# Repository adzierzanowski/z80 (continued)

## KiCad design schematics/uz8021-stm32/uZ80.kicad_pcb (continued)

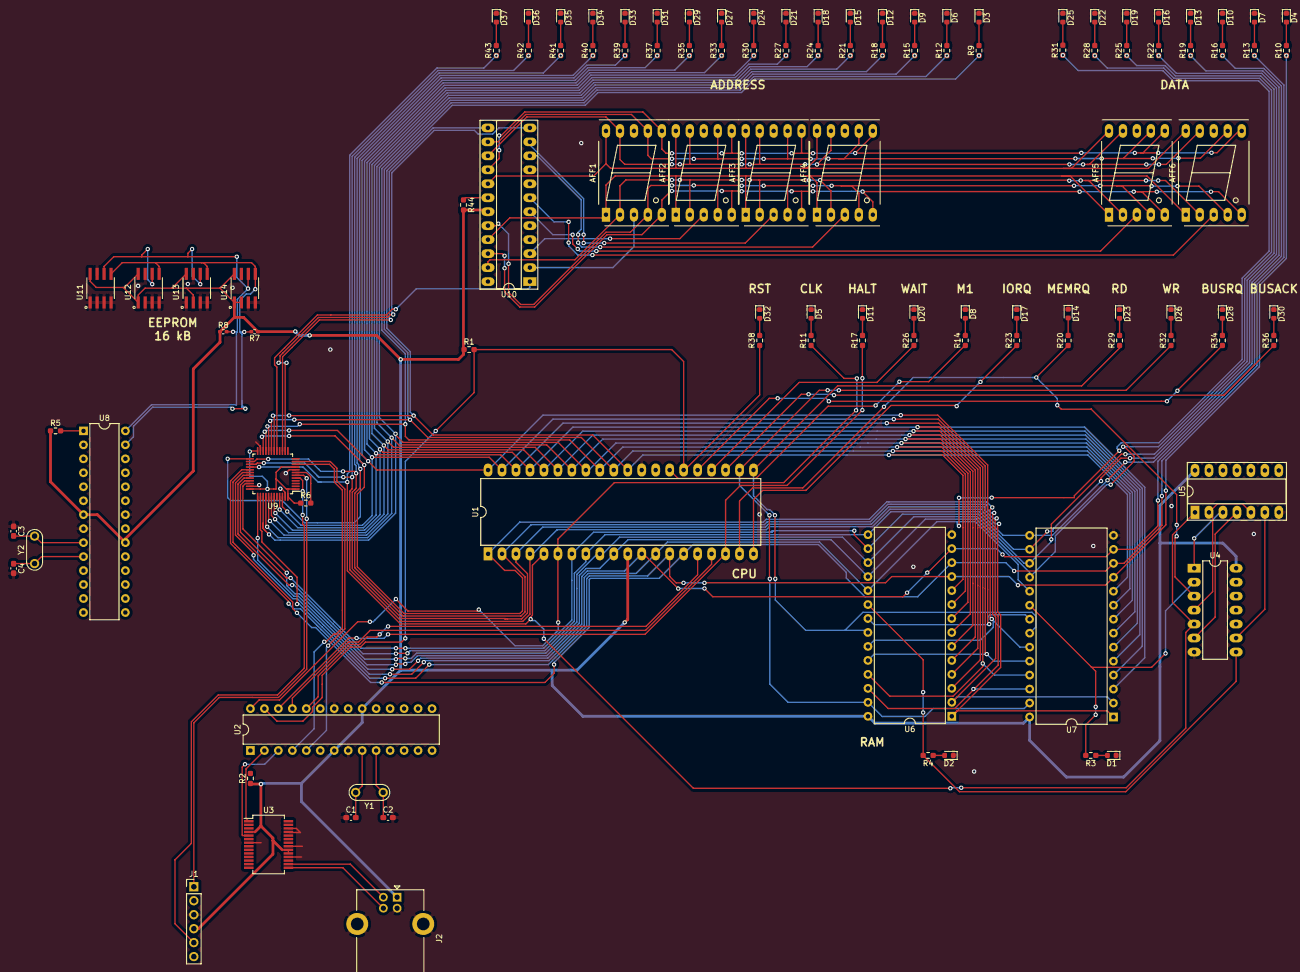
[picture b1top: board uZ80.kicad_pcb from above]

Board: 2 copper layers, 109 parts (0 on the bottom side), 118 nets.

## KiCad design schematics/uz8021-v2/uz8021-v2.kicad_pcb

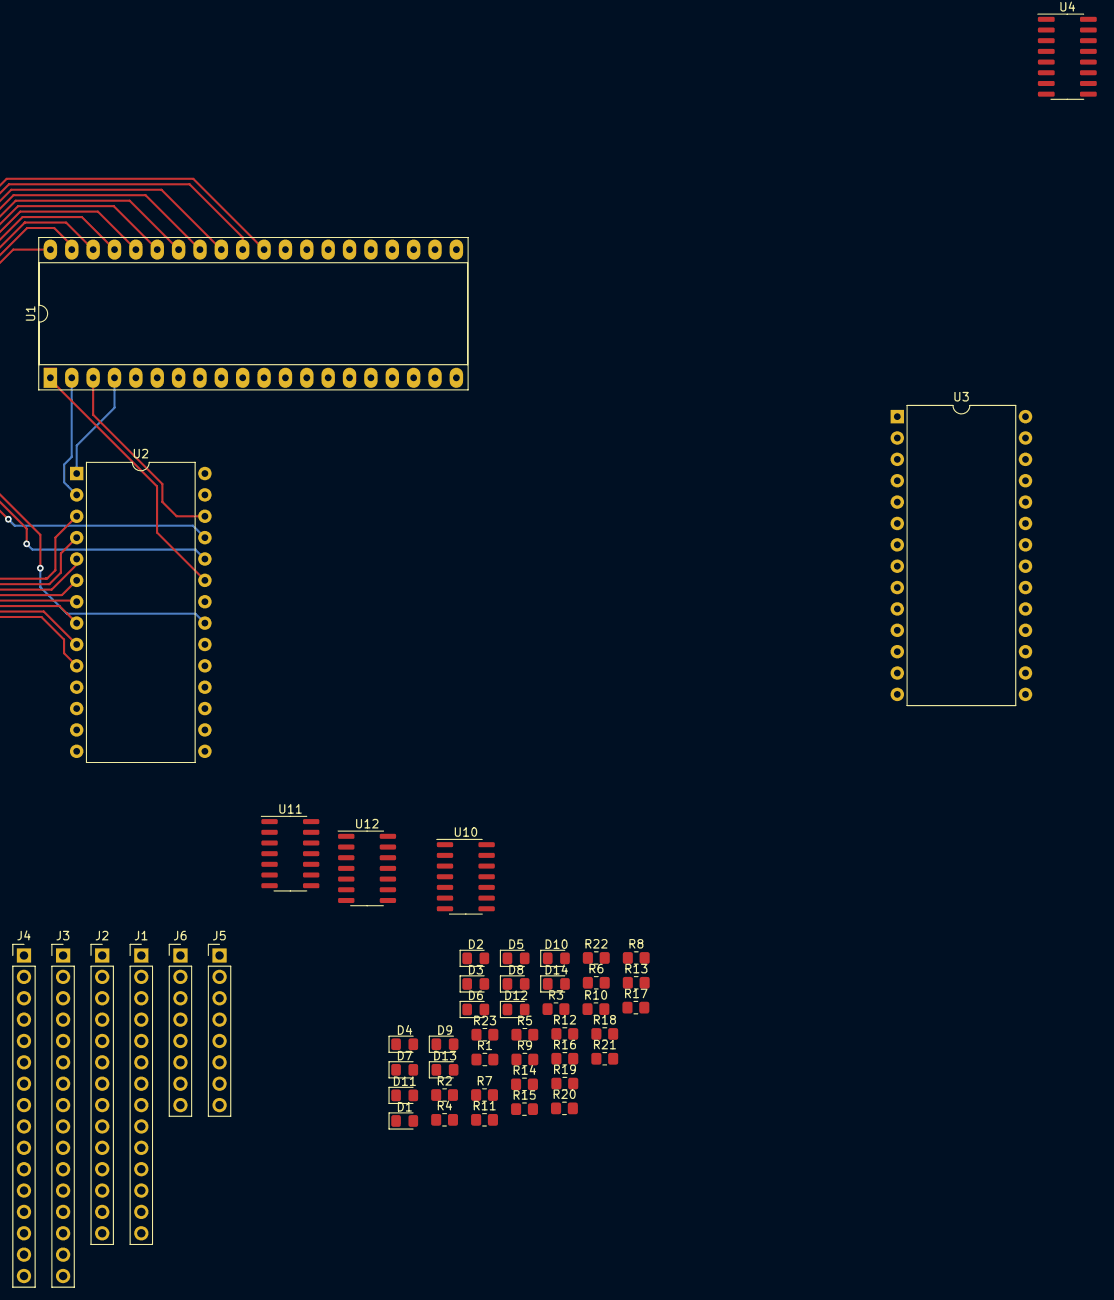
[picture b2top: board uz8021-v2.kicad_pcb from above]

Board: 2 copper layers, 50 parts (0 on the bottom side), 74 nets.

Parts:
D1, D2, D3, D4, D5, D6, D7, D8, D9, D10, D11, D12, D13, D14: LED; D_0805_2012Metric_Pad1.15x1.40mm_HandSolder
J1, J2: Conn_01x14_Male; PinHeader_1x14_P2.54mm_Vertical
J3, J4: Conn_01x16_Male; PinHeader_1x16_P2.54mm_Vertical
J5, J6: Conn_01x08_Male; PinHeader_1x08_P2.54mm_Vertical
R1, R2, R3, R4, R5, R6, R7, R8, R9: 10k; R_0805_2012Metric_Pad1.20x1.40mm_HandSolder
R10, R11, R12, R13, R14, R15, R16, R17, R18, R19, R20, R21, R22, R23: 330; R_0805_2012Metric_Pad1.20x1.40mm_HandSolder
U1: Z80CPU; DIP-40_W15.24mm_Socket_LongPads
U2, U3: CY62256-70PC; DIP-28_W15.24mm
U4: M52065; SOP-16_3.9x9.9mm_P1.27mm
U10, U11, U12: 74HC14; SO-14_3.9x8.65mm_P1.27mm

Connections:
+5V: R1.1, R2.1, R3.1, R4.1, R5.1, R6.1, R7.1, R8.1, R9.1, U1.11, U2.28, U3.28, U4.13, U10.14, U11.14, U12.14
/abus0: J3.1, J4.1, U1.30, U2.10, U3.10
/abus1: J3.2, J4.2, U1.31, U2.9, U3.9
/abus2: J3.3, J4.3, U1.32, U2.8, U3.8
/abus3: J3.4, J4.4, U1.33, U2.7, U3.7
/abus4: J3.5, J4.5, U1.34, U2.6, U3.6
/abus5: J3.6, J4.6, U1.35, U2.5, U3.5
/abus6: J3.7, J4.7, U1.36, U2.4, U3.4
/abus7: J3.8, J4.8, U1.37, U2.3, U3.3
/abus8: J3.9, J4.9, U1.38, U2.25, U3.25
/abus9: J3.10, J4.10, U1.39, U2.24, U3.24
/abus10: J3.11, J4.11, U1.40, U2.21, U3.21
/abus11: J3.12, J4.12, U1.1, U2.23, U3.23
/abus12: J3.13, J4.13, U1.2, U2.2, U3.2
/abus13: J3.14, J4.14, U1.3, U2.26, U3.26
/abus14: J3.15, J4.15, U1.4, U2.1, U3.1
/abus15: J3.16, J4.16, U1.5, U4.12, U12.9
/busack: J1.14, J2.14, U1.23, U12.3
/busrq: J1.13, J2.13, R9.2, U1.25, U12.1
/clk: J1.2, J2.2, U1.6, U10.3
/ctlbus0: J1.1, J2.1, R1.2, U1.26, U10.1
/ctlbus2: J1.3, J2.3, R2.2, U1.17, U10.5
/ctlbus3: J1.4, J2.4, R3.2, U1.16, U10.9
/ctlbus4: J1.5, J2.5, U1.27, U10.11
/ctlbus5: J1.6, J2.6, U1.28, U10.13
/ctlbus6: J1.7, J2.7, R4.2, U1.24, U11.1
/ctlbus7: J1.8, J2.8, U1.18, U11.3
/ctlbus8: J1.9, J2.9, R5.2, U1.21, U2.22, U3.22, U11.5
/ctlbus9: J1.10, J2.10, R6.2, U1.22, U2.27, U3.27, U11.9
/ctlbus10: J1.11, J2.11, R7.2, U1.19, U11.11, U12.5
/ctlbus11: J1.12, J2.12, R8.2, U1.20, U11.13
/dbus0: J5.1, J6.1, U1.14, U2.11, U3.11
/dbus1: J5.2, J6.2, U1.15, U2.12, U3.12
/dbus2: J5.3, J6.3, U1.12, U2.13, U3.13
/dbus3: J5.4, J6.4, U1.8, U2.15, U3.15
/dbus4: J5.5, J6.5, U1.7, U2.16, U3.16
/dbus5: J5.6, J6.6, U1.9, U2.17, U3.17
/dbus6: J5.7, J6.7, U1.10, U2.18, U3.18
/dbus7: J5.8, J6.8, U1.13, U2.19, U3.19
GND: D1.1, D2.1, D3.1, D4.1, D5.1, D6.1, D7.1, D8.1, D9.1, D10.1, D11.1, D12.1, D13.1, D14.1, U1.29, U2.14, U3.14, U4.4, U4.7, U4.8, U4.9, U4.10, U4.11, U4.15, U4.16, U10.7, U11.7, U12.7
unnamed: D1.2, R10.1
unnamed: D2.2, R11.1
unnamed: D3.2, R12.1
unnamed: D4.2, R13.1
unnamed: D5.2, R14.1
unnamed: D6.2, R15.1
unnamed: D7.2, R16.1
unnamed: D8.2, R17.1
unnamed: D9.2, R18.1
unnamed: D10.2, R19.1
unnamed: D11.2, R20.1
unnamed: D12.2, R21.1
unnamed: D13.2, R22.1
unnamed: D14.2, R23.1
unnamed: R10.2, U10.2
unnamed: R11.2, U10.4
unnamed: R12.2, U10.6
unnamed: R13.2, U10.8
unnamed: R14.2, U10.10
unnamed: R15.2, U10.12
unnamed: R16.2, U11.2
unnamed: R17.2, U11.4
unnamed: R18.2, U11.6
unnamed: R19.2, U11.8
unnamed: R20.2, U11.10
unnamed: R21.2, U11.12
unnamed: R22.2, U12.2
unnamed: R23.2, U12.4
unnamed: U4.2, U4.14, U12.6
unnamed: U4.1, U12.8
unnamed: U3.20, U12.10
unnamed: U4.3, U12.11
unnamed: U2.20, U12.12
unnamed: U4.5, U12.13

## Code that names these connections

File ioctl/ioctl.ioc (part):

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PB13.GPIOParameters=GPIO_Label
Mcu.UserName=STM32F072C8Tx
PB14.GPIO_Label=MEMRQ
PA9.GPIOParameters=GPIO_Label
PA11.Mode=Device
PB6.GPIO_Label=SEGDISP_CS
PA6.GPIO_Label=CLK
PC13.GPIO_Label=BUS_AL
PB13.GPIO_Label=BUSRQ
PB11.Signal=GPXTI11
PB13.Signal=GPIO_Output
PB15.Signal=GPIO_Input
PC15-OSC32_OUT.GPIO_Label=BUS_D
RCC.SYSCLKSource=RCC_SYSCLKSOURCE_HSI48
PA15.GPIO_Label=BUS_CS
PB4.GPIOParameters=GPIO_Label
PA12.Signal=USB_DP
PB6.Signal=GPIO_Output
PA8.GPIOParameters=GPIO_Label
PF0-OSC_IN.GPIO_Label=BUS_PL
PB2.Signal=GPIO_Output
PB3.Mode=TX_Only_Simplex_Unidirect_Master
PB12.GPIO_Label=BUSACK
PB1.GPIO_Label=INT
PB5.Mode=TX_Only_Simplex_Unidirect_Master
PA10.GPIO_Label=WR
PA8.Signal=GPIO_Output
PB6.GPIOParameters=GPIO_Label
PC14-OSC32_IN.GPIOParameters=GPIO_Label
Mcu.Package=LQFP48
PB9.Signal=I2C1_SDA
PA6.Signal=S_TIM16_CH1
PB1.Signal=GPIO_Output
PB11.GPIO_ModeDefaultEXTI=GPIO_MODE_IT_FALLING
PA10.Signal=GPIO_Input
PA15.Signal=GPIO_Output
PB14.GPIOParameters=GPIO_Label
PC14-OSC32_IN.GPIO_Label=BUS_AH
PB10.GPIOParameters=GPIO_Label
PC15-OSC32_OUT.GPIOParameters=GPIO_Label
PF1-OSC_OUT.Signal=GPIO_Output
PB4.Signal=GPIO_Output
PA6.GPIOParameters=GPIO_Label
PA15.GPIOParameters=GPIO_Label
PC13.Signal=GPIO_Input
PA9.GPIO_Label=RD
PB11.GPIO_Label=HLT
PC14-OSC32_IN.Signal=GPIO_Input
PA8.GPIO_Label=WAIT
PB10.GPIO_Label=NMI
PB9.Mode=I2C
PB2.GPIOParameters=GPIO_Label
PA9.Signal=GPIO_Input
PB11.GPIOParameters=GPIO_Label,GPIO_ModeDefaultEXTI
PC15-OSC32_OUT.Signal=GPIO_Input
PF1-OSC_OUT.GPIOParameters=GPIO_Label
PB10.Signal=GPIO_Output
PB14.Signal=GPIO_Input
board=custom
PB4.GPIO_Label=TFT_CS
PB15.GPIO_Label=IORQ
PC13.GPIOParameters=GPIO_Label
PF1-OSC_OUT.GPIO_Label=BUS_CP
PA10.GPIOParameters=GPIO_Label
PB15.GPIOParameters=GPIO_Label
Mcu.Name=STM32F072C(8-B)Tx
PB3.Signal=SPI1_SCK
RCC.SYSCLKFreq_VALUE=48000000
PB5.Signal=SPI1_MOSI
PA7.GPIO_Label=RST
PA12.Mode=Device
PA11.Signal=USB_DM
PB2.GPIO_Label=LED
PB8.Mode=I2C
PB8.Signal=I2C1_SCL
PF0-OSC_IN.Signal=GPIO_Output
PF0-OSC_IN.GPIOParameters=GPIO_Label
PA7.GPIOParameters=GPIO_Label
PB12.GPIOParameters=GPIO_Label
PB12.Signal=GPIO_Input
PB1.GPIOParameters=GPIO_Label
PA7.Signal=GPIO_Output

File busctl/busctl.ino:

#define LC_DIN 2
#define LC_LOAD 3
#define LC_CLK 4

#define BUSRQ 22
#define BUSACK 24
#define DBUS0 38

#define ABUS0 23

#define MEMRQ 26
#define IORQ 28
#define WAIT 30
#define RD 32
#define WR 34

#define BTN 7


#include "LedControl.h"

bool progMode = false;

LedControl lc(LC_DIN, LC_CLK, LC_LOAD, 1);

const uint8_t program[] = {
  0b00110001, 0, 0b00010000,
  0b00111110, 0b10101010,
  0b1110110,
  0b11000011, 0b11, 0
};

const size_t program_sz = sizeof program / sizeof program[0];

void waitForButton() {
  static uint32_t debounce = 0;
  while (true) {
    if (millis() - debounce > 200 && !digitalRead(BTN)) {
      break;
    }
  }
  debounce = millis();
}

uint16_t readAddr() {
  uint16_t val = 0;
  for (int i = 0; i < 16; i++) {
    val |= digitalRead(ABUS0 + i*2) << i;
  }
  return val;
}

uint8_t readData() {
  uint8_t val = 0;
  for (int i = 0; i < 8; i++) {
    val |= digitalRead(DBUS0 + i*2) << i;
  }
  return val;
}

void setData(uint8_t val) {
  for (int i = 0; i < 8; i++) {
    digitalWrite(DBUS0 + i*2, !!(val & (1 << i)));
  }
}

void setDataIn() {
  for (int i = DBUS0; i < DBUS0 + 8*2; i+=2) {
    pinMode(i, INPUT);
  }
}

void setDataOut() {
  for (int i = DBUS0; i < DBUS0 + 8*2; i+=2) {
    pinMode(i, OUTPUT);
  }
}

void setAddr(uint16_t val) {
  for (int i = 0; i < 16; i++) {
    digitalWrite(ABUS0 + i*2, !!(val & (1 << i)));
  }
}

void ramWrite(uint16_t addr, uint8_t val) {
  setAddr(addr);
  delay(1);
  setData(val);
  delay(1);
  digitalWrite(MEMRQ, LOW);
  delay(1);
  digitalWrite(WR, LOW);
  delay(1);
  digitalWrite(WR, HIGH);
  delay(1);
  digitalWrite(MEMRQ, HIGH);
  delay(1);
}

bool acquireBus() {
  digitalWrite(BUSRQ, LOW);
  while (digitalRead(BUSACK)) {}
  delay(100);

  for (int i = ABUS0; i < ABUS0 + 16*2; i+=2) {
    pinMode(i, OUTPUT);
  }

  for (int i = DBUS0; i < DBUS0 + 8*2; i+=2) {
    pinMode(i, OUTPUT);
  }

  pinMode(MEMRQ, OUTPUT);
  pinMode(RD, OUTPUT);
  pinMode(WR, OUTPUT);

  digitalWrite(MEMRQ, HIGH);
  digitalWrite(RD, HIGH);
  digitalWrite(WR, HIGH);
}

void releaseBus() {
  for (int i = ABUS0; i < ABUS0 + 16*2; i+=2) {
    pinMode(i, INPUT);
  }
  for (int i = DBUS0; i < DBUS0 + 8*2; i+=2) {
    pinMode(i, INPUT);
  }
  pinMode(MEMRQ, INPUT);
  pinMode(RD, INPUT);
  pinMode(WR, INPUT);

  delay(100);

  digitalWrite(BUSRQ, HIGH);
}

void setup() {
  Serial.begin(115200);

  pinMode(BUSACK, INPUT);
  pinMode(BUSRQ, OUTPUT);
  pinMode(MEMRQ, INPUT);
  pinMode(RD, INPUT);
  pinMode(WR, INPUT);
  pinMode(WAIT, OUTPUT);
  pinMode(BTN, INPUT_PULLUP);

  digitalWrite(WAIT, HIGH);
  digitalWrite(BUSRQ, HIGH);

  for (int i = ABUS0; i < ABUS0 + 16*2; i+=2) {
    pinMode(i, INPUT);
  }

  for (int i = DBUS0; i < DBUS0 + 8*2; i+=2) {
    pinMode(i, INPUT);
  }

  lc.shutdown(0,false);
  lc.setIntensity(0,0xf);
  lc.clearDisplay(0);
}

void loop() {

  if (progMode) {
    acquireBus();

    Serial.println('ok');

    bool probableStop = false;
    uint16_t addr = 0;

    while (true) {
      if (Serial.available()) {
        uint8_t c = (uint8_t) Serial.read();

        if (c == 0xdd) {
          probableStop = true;
        } else if (probableStop) {
          if (c == 0x64) { // ld ixh, ixh (basically nop)
            progMode = false;
          } else {
            probableStop = false;
          }
        }

        ramWrite(addr++, c);
        Serial.write(c);
        //Serial.flush();

        if (!progMode) {
          Serial.println('done');
          break;
        }
      }
    }

    releaseBus();
    progMode = false;

  } else {
    if (Serial.available()) {
      char c = Serial.read();
      if (c == 'p') {
        progMode = true;
      }
    }

    uint8_t data = readData();
    uint16_t addr = readAddr();

    lc.setDigit(0, 0, data >> 4, false);
    lc.setDigit(0, 1, data & 0xf, false);

    lc.setDigit(0, 2, (addr >> 4) & 0xf, false);
    lc.setDigit(0, 3, (addr >> 0) & 0xf, false);
    lc.setDigit(0, 4, (addr >> 12) & 0xf, false);
    lc.setDigit(0, 5, (addr >> 8) & 0xf, false);

    delay(10);
  }
}

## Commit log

2021-09-22 init
2021-09-22 memenu
2021-09-22 py scripts
2021-09-22 readme
2021-09-22 gitignore
2021-09-22 delete
2021-09-23 asm refactor
2021-09-25 assembler rewrite
2021-09-25 debugging session
2021-09-25 includes
2021-09-26 disassembler;
2021-09-26 fix opcodes with operands inbetween bytes
2021-09-26 prettify disasm output; make package installable
2021-09-27 mostly assembler fixes
2021-09-27 fix relative jumps
2021-10-12 z80asm bugfixing and minor features
2021-10-12 kicad schematics
2021-10-12 rm vscode
2021-10-12 serialprompt
2021-10-12 large update
2021-10-12 rm ds_store
2021-10-12 readme update
2021-10-16 includes, org directive, once directive, def directive, missing mnemonics
2022-02-10 honestly, I dont know
